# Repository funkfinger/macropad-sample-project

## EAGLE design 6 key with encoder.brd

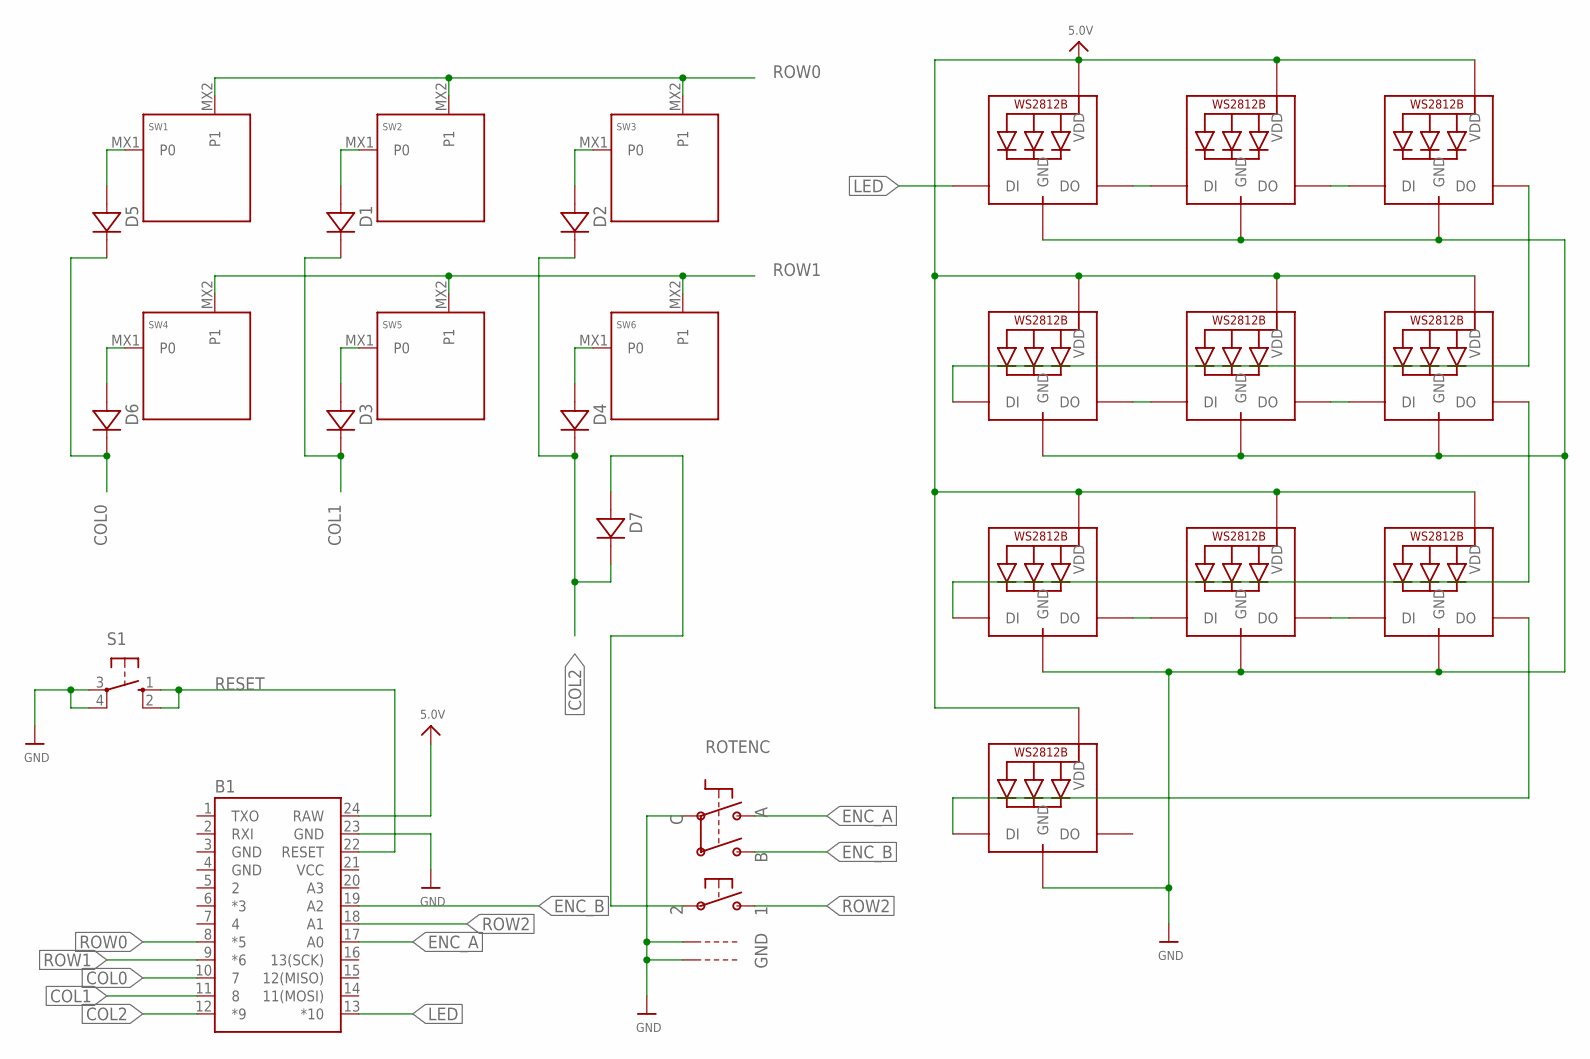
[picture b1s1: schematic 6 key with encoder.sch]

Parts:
B1: SPARKFUN_PRO_MICRO
D1, D2, D3, D4, D5, D6, D7: DIODE-SOD-123; SOD-123
LED1, LED2, LED3, LED4, LED5, LED6, LED7, LED8, LED9, LED10: WS2812B_SK6812E; NEO3535_REVERSE
ROTENC: ENCODER_PLUS_SWITCH_BOURNS_PEC11; PEC11+SWITCH
S1: 10-XX; B3F-10XX
SW1, SW2, SW3, SW4, SW5, SW6: KEYSWITCH-PLAIN-MXHS-1U; MXHS-1U

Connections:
5.0V: B1.24 (RAW), LED1.1-VDD (VDD), LED2.1-VDD (VDD), LED3.1-VDD (VDD), LED4.1-VDD (VDD), LED5.1-VDD (VDD), LED6.1-VDD (VDD), LED7.1-VDD (VDD), LED8.1-VDD (VDD), LED9.1-VDD (VDD), LED10.1-VDD (VDD)
COL0: B1.10 (7), D5.C, D6.C
COL1: B1.11 (8), D1.C, D3.C
COL2: B1.12 (*9), D2.C, D4.C, D7.C
ENC_A: B1.17 (A0), ROTENC.P$A
ENC_B: B1.19 (A2), ROTENC.P$B
GND: B1.3 (GND), B1.4 (GND), B1.23 (GND), LED1.3-GND (GND), LED2.3-GND (GND), LED3.3-GND (GND), LED4.3-GND (GND), LED5.3-GND (GND), LED6.3-GND (GND), LED7.3-GND (GND), LED8.3-GND (GND), LED9.3-GND (GND), LED10.3-GND (GND), ROTENC.P$C, ROTENC.P$GND1, ROTENC.P$GND2, S1.3, S1.4 (P1)
LED: B1.13 (*10), LED1.4-DIN (DI)
unnamed: D5.A, SW1.MX1 (P0)
unnamed: D6.A, SW4.MX1 (P0)
unnamed: D3.A, SW5.MX1 (P0)
unnamed: D1.A, SW2.MX1 (P0)
unnamed: D2.A, SW3.MX1 (P0)
unnamed: D4.A, SW6.MX1 (P0)
unnamed: D7.A, ROTENC.P$2
unnamed: LED1.2-DOUT (DO), LED2.4-DIN (DI)
unnamed: LED2.2-DOUT (DO), LED3.4-DIN (DI)
unnamed: LED3.2-DOUT (DO), LED4.4-DIN (DI)
unnamed: LED4.2-DOUT (DO), LED5.4-DIN (DI)
unnamed: LED5.2-DOUT (DO), LED6.4-DIN (DI)
unnamed: LED6.2-DOUT (DO), LED7.4-DIN (DI)
unnamed: LED7.2-DOUT (DO), LED8.4-DIN (DI)
unnamed: LED8.2-DOUT (DO), LED9.4-DIN (DI)
unnamed: LED9.2-DOUT (DO), LED10.4-DIN (DI)
RESET: B1.22 (RESET), S1.1 (S), S1.2 (S1)
ROW0: B1.8 (*5), SW1.MX2 (P1), SW2.MX2 (P1), SW3.MX2 (P1)
ROW1: B1.9 (*6), SW4.MX2 (P1), SW5.MX2 (P1), SW6.MX2 (P1)
ROW2: B1.18 (A1), ROTENC.P$1
VCC: B1.21 (VCC)

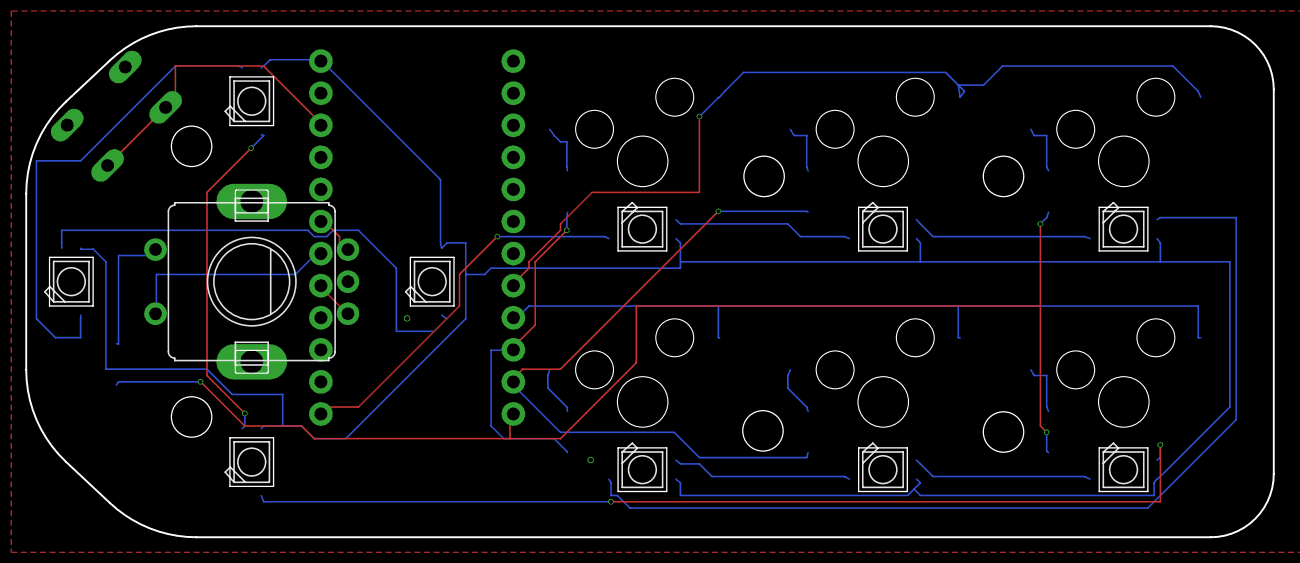
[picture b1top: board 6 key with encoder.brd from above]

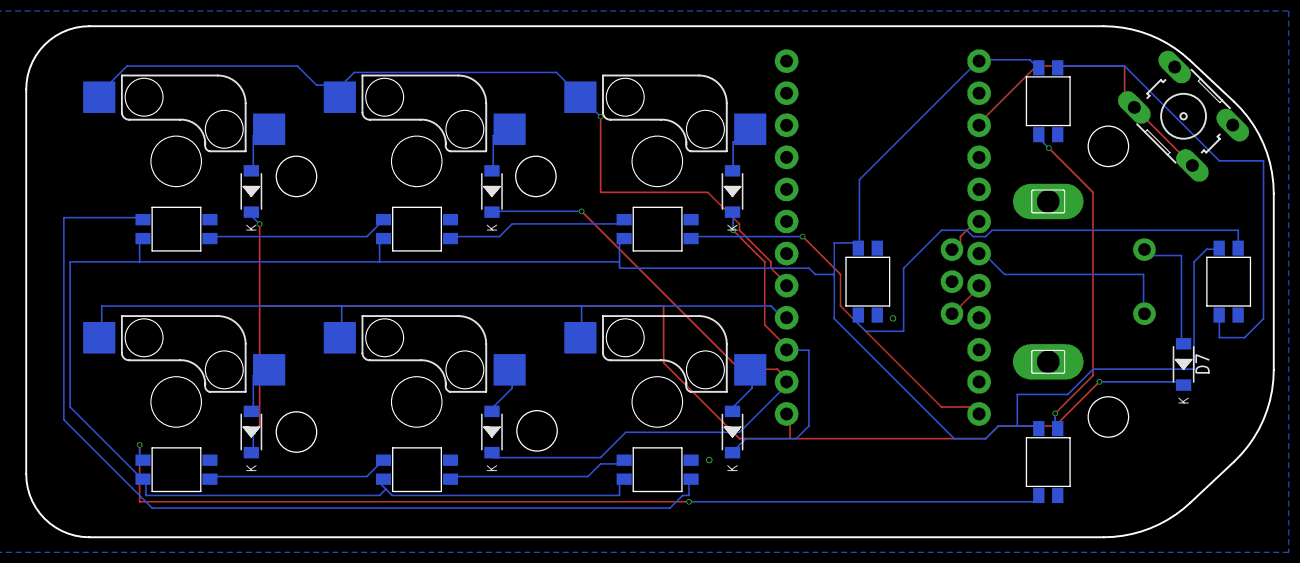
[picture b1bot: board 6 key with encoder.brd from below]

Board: 2 copper layers, 98.8 x 40.5 mm, 26 parts (15 on the bottom side), 28 nets.

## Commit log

2021-11-18 removing temp files
2021-11-18 adding gitignore
2021-11-20 updates to board
2021-11-22 tweaks
2021-12-06 production 12-6-2021
